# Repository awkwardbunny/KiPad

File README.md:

# KiPad

Custom keypad made using KiCad.

Custom PCB + 3D printed keycaps and case.

# PCB

The PCB was designed in KiCad and manufactured by JLCPCB.

Most of the components have a custom field `DIGIKEY`, which corresponds to the Digikey part number.
Components can be ordered from Digikey easily by doing a BOM export and using Digikey's upload list feature.

The hotswap connectors, key switches, and stablizers do not have Digikey part numbers. Choose ones you like.

# Keycaps

The keycaps were generated using [this library](https://github.com/rsheldiii/KeyV2).

# Case

The PCB was exported from KiCad and a case was modeled around it using OnShape. The models can be found under [case/](/case) or on [OnShape](https://cad.onshape.com/documents/05e5af1ac1cd92aec3ff415b/w/62ce95e3d910c49c77b0c6ec/e/b1757f7efc67fc1a5c9fca3c?renderMode=0&uiState=66b20bf3e3c77e6059daf154).

The bottom of the case is designed to fit 1.2mm thick boards, so keep that in mind when putting in the PCB order.

# Firmware

To build the firmware, follow the [QMK setup](https://docs.qmk.fm/newbs_getting_started), and then copy/link the `qmk` directory into the keyboards directory:

```bash
# Clone project
git clone https://github.com/awkwardbunny/KiPad
cd KiPad
# By default, QMK installs to ~/qmk_firmware on linux
ln -s $(pwd)/qmk ~/qmk_firmware/keyboards/meirl
# Flash. Use the directory name above
qmk flash -kb meirl/kipad_v3_1 -km via
```

## Reset and DFU

The Atmega32u2 goes into DFU bootloader without any code on it. If you wish to reflash, connect the keypad while holding down the top-left key (A).

If a bad firmware was uploaded and you cannot get it into DFU mode with that method, you need to trigger a reset while the `HWB` pin is pulled low.
There is a pad exposed on the back for reset, and the `HWB` pin is connected to column 3. I solder one wire to each of these and do the following:

1. Connect the device
2. Take the wire connected to column 3 and make contact with ground (the USb shield works)
3. Touch the wire connected to the reset pin briefly to ground
4. Release the column 3 wire

And the device should show up in DFU mode

## Via

To use with [Via](https://usevia.app/), you need to enable `Settings -> Show design tab -> Enable`. A new tab should appear.
Open the new design tab and upload the keyboard definition [qmk/kipad_v3_1/via.json](/qmk/kipad_v3_1/via.json). Now you should be able to reconfigure it as you like.

### Udev

For linux, Via may not be able to access the keypad HID devices due to permissions. Try adding the following to `/etc/udev/rules.d/90-kipad.rules`:
```
# MEIRL KiPad v2.0
SUBSYSTEM=="usb", ATTRS{idVendor}=="4248", ATTRS{idProduct}=="4b50", MODE="0666"
KERNEL=="hidraw*", ATTRS{busnum}=="1", ATTRS{idVendor}=="4248", ATTRS{idProduct}=="4b50", MODE="0666"

# MEIRL KiPad v3.0
SUBSYSTEM=="usb", ATTRS{idVendor}=="4248", ATTRS{idProduct}=="4b51", MODE="0666"
KERNEL=="hidraw*", ATTRS{busnum}=="1", ATTRS{idVendor}=="4248", ATTRS{idProduct}=="4b51", MODE="0666"

# MEIRL KiPad v3.1
SUBSYSTEM=="usb", ATTRS{idVendor}=="4248", ATTRS{idProduct}=="4b52", MODE="0666"
KERNEL=="hidraw*", ATTRS{busnum}=="1", ATTRS{idVendor}=="4248", ATTRS{idProduct}=="4b52", MODE="0666"
```

And then `sudo udevadm control --reload`.

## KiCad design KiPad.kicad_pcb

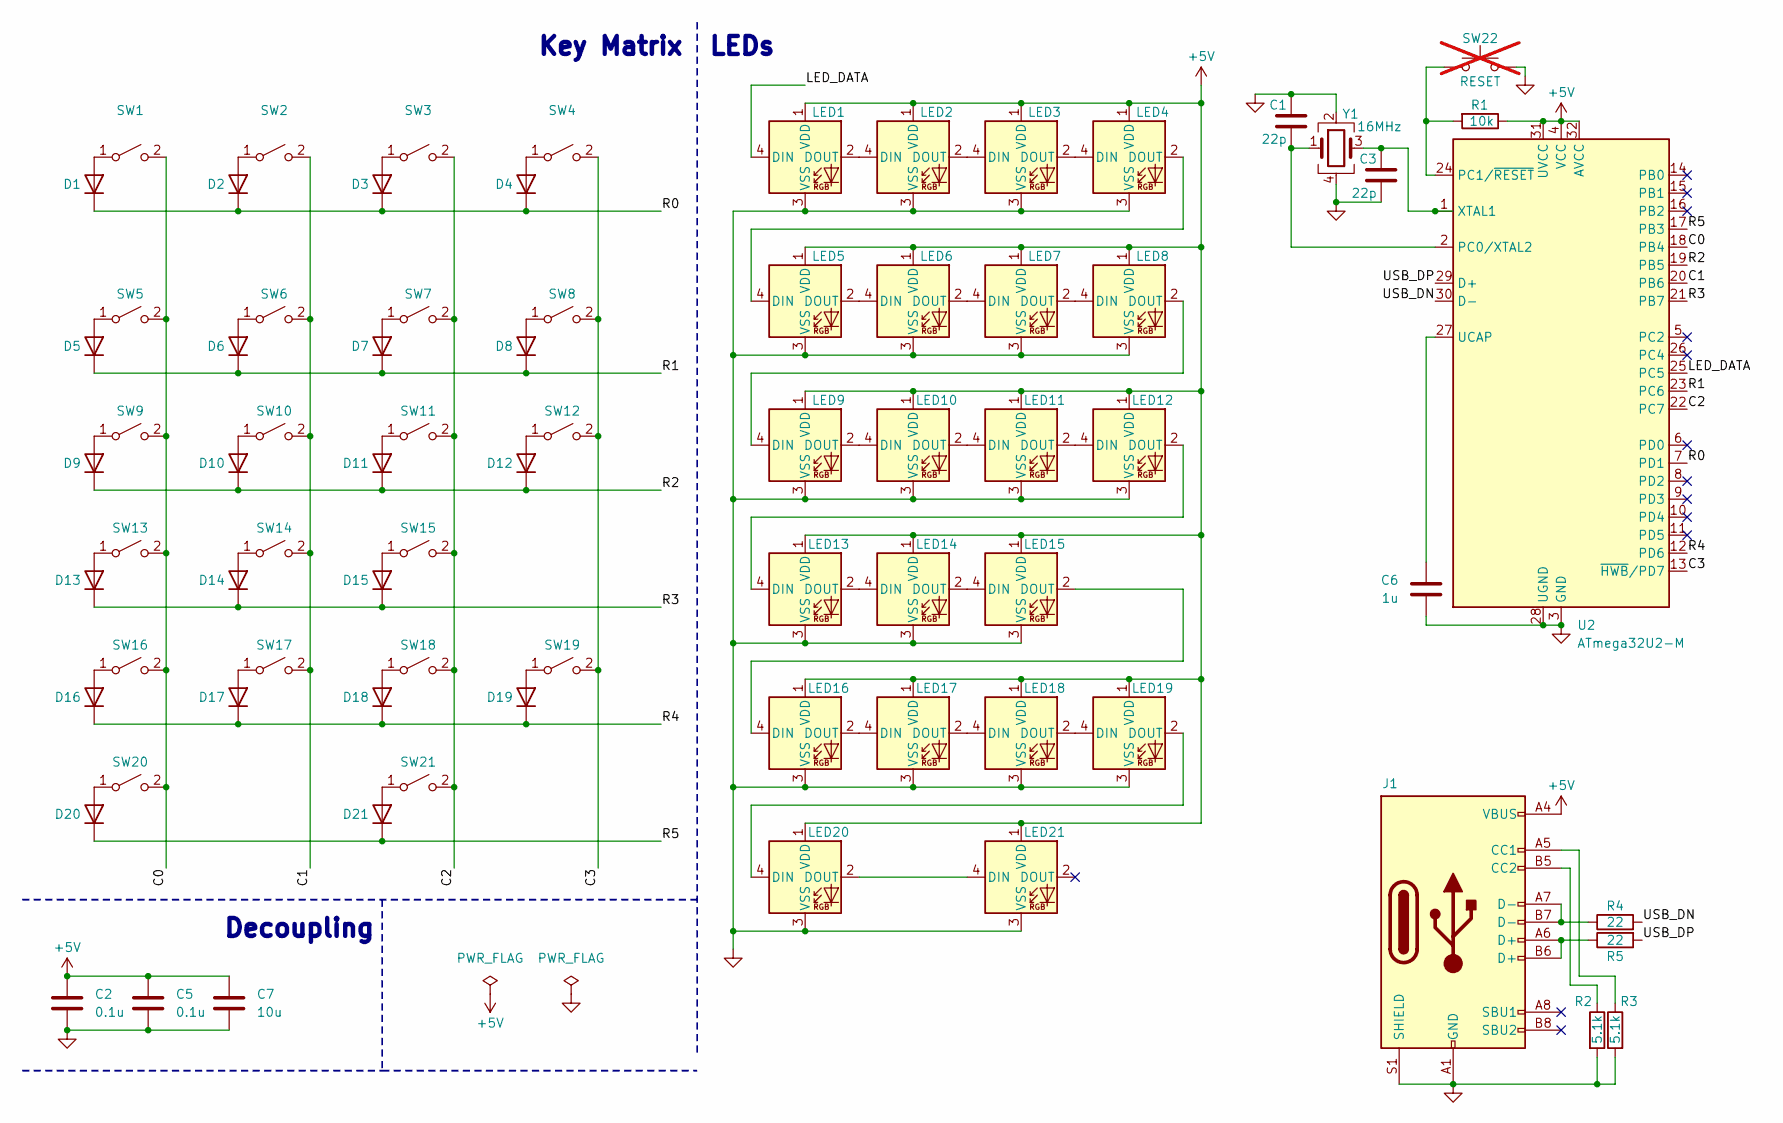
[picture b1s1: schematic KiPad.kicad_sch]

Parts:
C1, C3: 22p; C_0402_1005Metric; DIGIKEY 490-9648-1-ND
C2, C5: 0.1u; C_0805_2012Metric; DIGIKEY 478-KGM21NR71H104KTTR-ND
C6: 1u; C_0603_1608Metric; DIGIKEY 311-1446-1-ND
C7: 10u; C_0805_2012Metric; DIGIKEY 587-1300-1-ND
D1, D2, D3, D4, D5, D6, D7, D8, D9, D10, D11, D12, D13, D14, D15, D16, D17, D18, D19, D20, D21: D_MiniMELF; DIGIKEY FDLL4148TR-ND
J1: USB_C_Receptacle_USB2.0_14P; USB_C_Receptacle_GCT_USB4105-xx-A_16P_TopMnt_Horizontal; DIGIKEY 2073-USB4105-GF-ACT-ND
LED1, LED2, LED3, LED4, LED5, LED6, LED7, LED8, LED9, LED10, LED11, LED12, LED13, LED14, LED15, LED16, LED17, LED18, LED19, LED20, LED21: SK6812MINI; LED_SK6812MINI-E_PLCC4_3.2x2.8mm_P1.75mm; DIGIKEY 1528-4960-ND
R1: 10k; R_0402_1005Metric; DIGIKEY 311-10KJRCT-ND
R2, R3: 5.1k; R_0402_1005Metric; DIGIKEY P5.1KJCT-ND
R4, R5: 22; R_0402_1005Metric; DIGIKEY 311-22.0LRCT-ND
SW1: SW_A; MX-Hotswap-1U
SW2: SW_B; MX-Hotswap-1U
SW3: SW_C; MX-Hotswap-1U
SW4: SW_D; MX-Hotswap-1U
SW5: SW_NL; MX-Hotswap-1U
SW6: SW_DIV; MX-Hotswap-1U
SW7: SW_MUL; MX-Hotswap-1U
SW8: SW_SUB; MX-Hotswap-1U
SW9: SW_7; MX-Hotswap-1U
SW10: SW_8; MX-Hotswap-1U
SW11: SW_9; MX-Hotswap-1U
SW12: SW_ADD; MX-Hotswap-2U-Vertical
SW13: SW_4; MX-Hotswap-1U
SW14: SW_5; MX-Hotswap-1U
SW15: SW_6; MX-Hotswap-1U
SW16: SW_1; MX-Hotswap-1U
SW17: SW_2; MX-Hotswap-1U
SW18: SW_3; MX-Hotswap-1U
SW19: SW_ENTER; MX-Hotswap-2U-Vertical
SW20: SW_0; MX-Hotswap-2U-ReversedStabilizers
SW21: SW_DOT; MX-Hotswap-1U
SW22: RESET; R_0402_1005Metric_Pad0.72x0.64mm_HandSolder; not fitted
U2: ATmega32U2-M; QFN-32-1EP_5x5mm_P0.5mm_EP3.1x3.1mm; DIGIKEY ATMEGA32U2-MURCT-ND
Y1: 16MHz; Crystal_SMD_3225-4Pin_3.2x2.5mm; DIGIKEY 535-14031-1-ND

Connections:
+5V: C2.1, C5.1, C7.1, J1.A4 (VBUS), J1.A9 (VBUS), J1.B4 (VBUS), J1.B9 (VBUS), LED1.1 (VDD), LED2.1 (VDD), LED3.1 (VDD), LED4.1 (VDD), LED5.1 (VDD), LED6.1 (VDD), LED7.1 (VDD), LED8.1 (VDD), LED9.1 (VDD), LED10.1 (VDD), LED11.1 (VDD), LED12.1 (VDD), LED13.1 (VDD), LED14.1 (VDD), LED15.1 (VDD), LED16.1 (VDD), LED17.1 (VDD), LED18.1 (VDD), LED19.1 (VDD), LED20.1 (VDD), LED21.1 (VDD), R1.1, U2.4 (VCC), U2.31 (UVCC), U2.32 (AVCC)
/C0: SW1.2 (B), SW5.2 (B), SW9.2 (B), SW13.2 (B), SW16.2 (B), SW20.2 (B), U2.18 (PB4)
/C1: SW2.2 (B), SW6.2 (B), SW10.2 (B), SW14.2 (B), SW17.2 (B), U2.20 (PB6)
/C2: SW3.2 (B), SW7.2 (B), SW11.2 (B), SW15.2 (B), SW18.2 (B), SW21.2 (B), U2.22 (PC7)
/C3: SW4.2 (B), SW8.2 (B), SW12.2 (B), SW19.2 (B), U2.13 (~HWB/PD7)
/LED_DATA: LED1.4 (DIN), U2.25 (PC5)
/R0: D1.1 (K), D2.1 (K), D3.1 (K), D4.1 (K), U2.7 (PD1)
/R1: D5.1 (K), D6.1 (K), D7.1 (K), D8.1 (K), U2.23 (PC6)
/R2: D9.1 (K), D10.1 (K), D11.1 (K), D12.1 (K), U2.19 (PB5)
/R3: D13.1 (K), D14.1 (K), D15.1 (K), U2.21 (PB7)
/R4: D16.1 (K), D17.1 (K), D18.1 (K), D19.1 (K), U2.12 (PD6)
/R5: D20.1 (K), D21.1 (K), U2.17 (PB3)
/USB_DN: R4.2, U2.30 (D-)
/USB_DP: R5.2, U2.29 (D+)
GND: C1.1, C2.2, C3.2, C5.2, C6.2, C7.2, J1.A1 (GND), J1.A12 (GND), J1.B1 (GND), J1.B12 (GND), J1.S1 (SHIELD), LED1.3 (VSS), LED2.3 (VSS), LED3.3 (VSS), LED4.3 (VSS), LED5.3 (VSS), LED6.3 (VSS), LED7.3 (VSS), LED8.3 (VSS), LED9.3 (VSS), LED10.3 (VSS), LED11.3 (VSS), LED12.3 (VSS), LED13.3 (VSS), LED14.3 (VSS), LED15.3 (VSS), LED16.3 (VSS), LED17.3 (VSS), LED18.3 (VSS), LED19.3 (VSS), LED20.3 (VSS), LED21.3 (VSS), R2.2, R3.2, SW22.2, U2.3 (GND), U2.28 (UGND), U2.33 (GND), Y1.2, Y1.4
unnamed: D1.2 (A), SW1.1 (A)
unnamed: D2.2 (A), SW2.1 (A)
unnamed: D3.2 (A), SW3.1 (A)
unnamed: D4.2 (A), SW4.1 (A)
unnamed: D5.2 (A), SW5.1 (A)
unnamed: D6.2 (A), SW6.1 (A)
unnamed: D7.2 (A), SW7.1 (A)
unnamed: D8.2 (A), SW8.1 (A)
unnamed: D9.2 (A), SW9.1 (A)
unnamed: D10.2 (A), SW10.1 (A)
unnamed: D11.2 (A), SW11.1 (A)
unnamed: D12.2 (A), SW12.1 (A)
unnamed: D13.2 (A), SW13.1 (A)
unnamed: D14.2 (A), SW14.1 (A)
unnamed: D15.2 (A), SW15.1 (A)
unnamed: D16.2 (A), SW16.1 (A)
unnamed: D17.2 (A), SW17.1 (A)
unnamed: D18.2 (A), SW18.1 (A)
unnamed: D19.2 (A), SW19.1 (A)
unnamed: D20.2 (A), SW20.1 (A)
unnamed: D21.2 (A), SW21.1 (A)
unnamed: J1.A5 (CC1), R3.1
unnamed: J1.B5 (CC2), R2.1
unnamed: J1.A6 (D+), J1.B6 (D+), R5.1
unnamed: J1.A7 (D-), J1.B7 (D-), R4.1
unnamed: LED1.2 (DOUT), LED2.4 (DIN)
unnamed: LED2.2 (DOUT), LED3.4 (DIN)
unnamed: LED3.2 (DOUT), LED4.4 (DIN)
unnamed: LED4.2 (DOUT), LED5.4 (DIN)
unnamed: LED5.2 (DOUT), LED6.4 (DIN)
unnamed: LED6.2 (DOUT), LED7.4 (DIN)
unnamed: LED7.2 (DOUT), LED8.4 (DIN)
unnamed: LED8.2 (DOUT), LED9.4 (DIN)
unnamed: LED9.2 (DOUT), LED10.4 (DIN)
unnamed: LED10.2 (DOUT), LED11.4 (DIN)
unnamed: LED11.2 (DOUT), LED12.4 (DIN)
unnamed: LED12.2 (DOUT), LED13.4 (DIN)
unnamed: LED13.2 (DOUT), LED14.4 (DIN)
unnamed: LED14.2 (DOUT), LED15.4 (DIN)
unnamed: LED15.2 (DOUT), LED16.4 (DIN)
unnamed: LED16.2 (DOUT), LED17.4 (DIN)
unnamed: LED17.2 (DOUT), LED18.4 (DIN)
unnamed: LED18.2 (DOUT), LED19.4 (DIN)
unnamed: LED19.2 (DOUT), LED20.4 (DIN)
unnamed: LED20.2 (DOUT), LED21.4 (DIN)
unnamed: C1.2, U2.2 (PC0/XTAL2), Y1.1
unnamed: R1.2, SW22.1, U2.24 (PC1/~RESET)
unnamed: C6.1, U2.27 (UCAP)
unnamed: C3.1, U2.1 (XTAL1), Y1.3

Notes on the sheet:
Key Matrix
LEDs
Decoupling

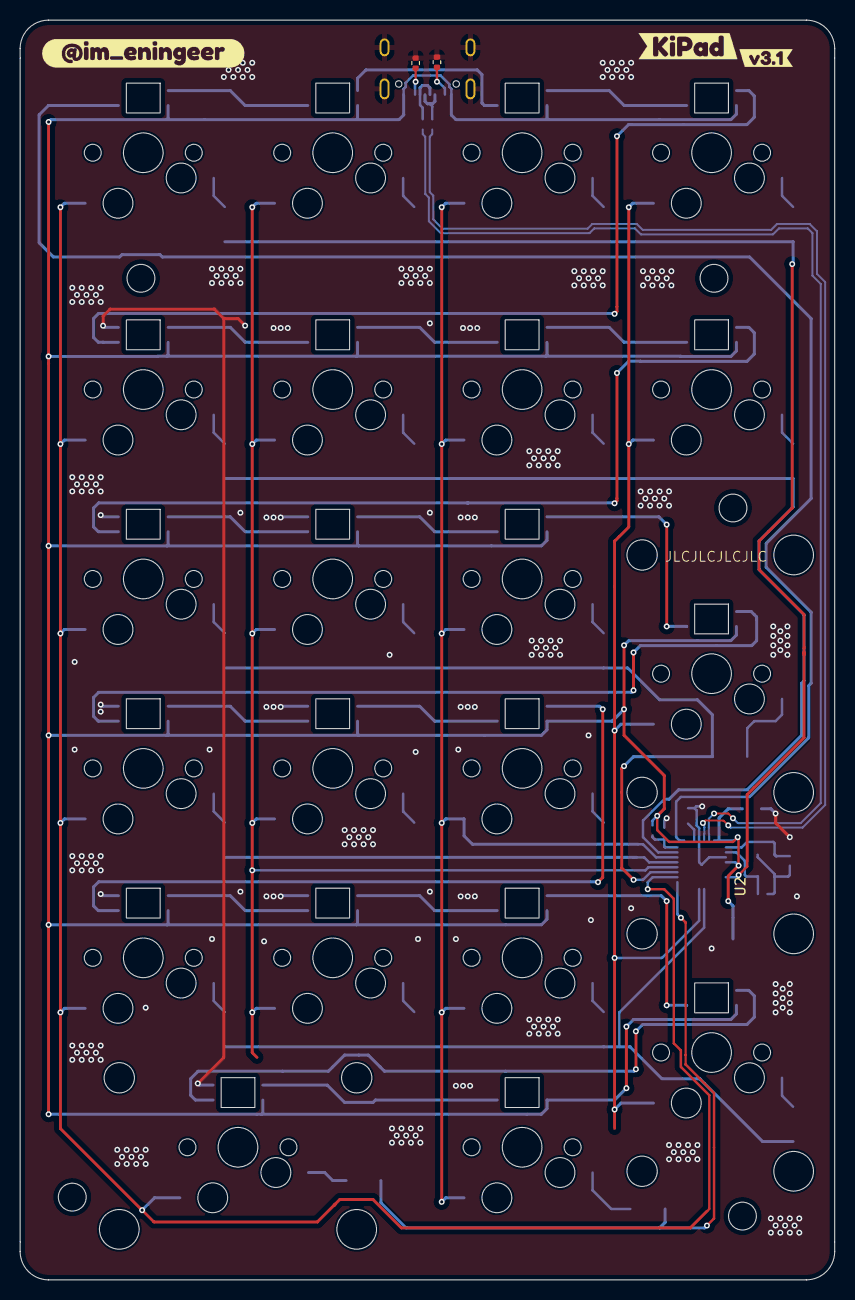
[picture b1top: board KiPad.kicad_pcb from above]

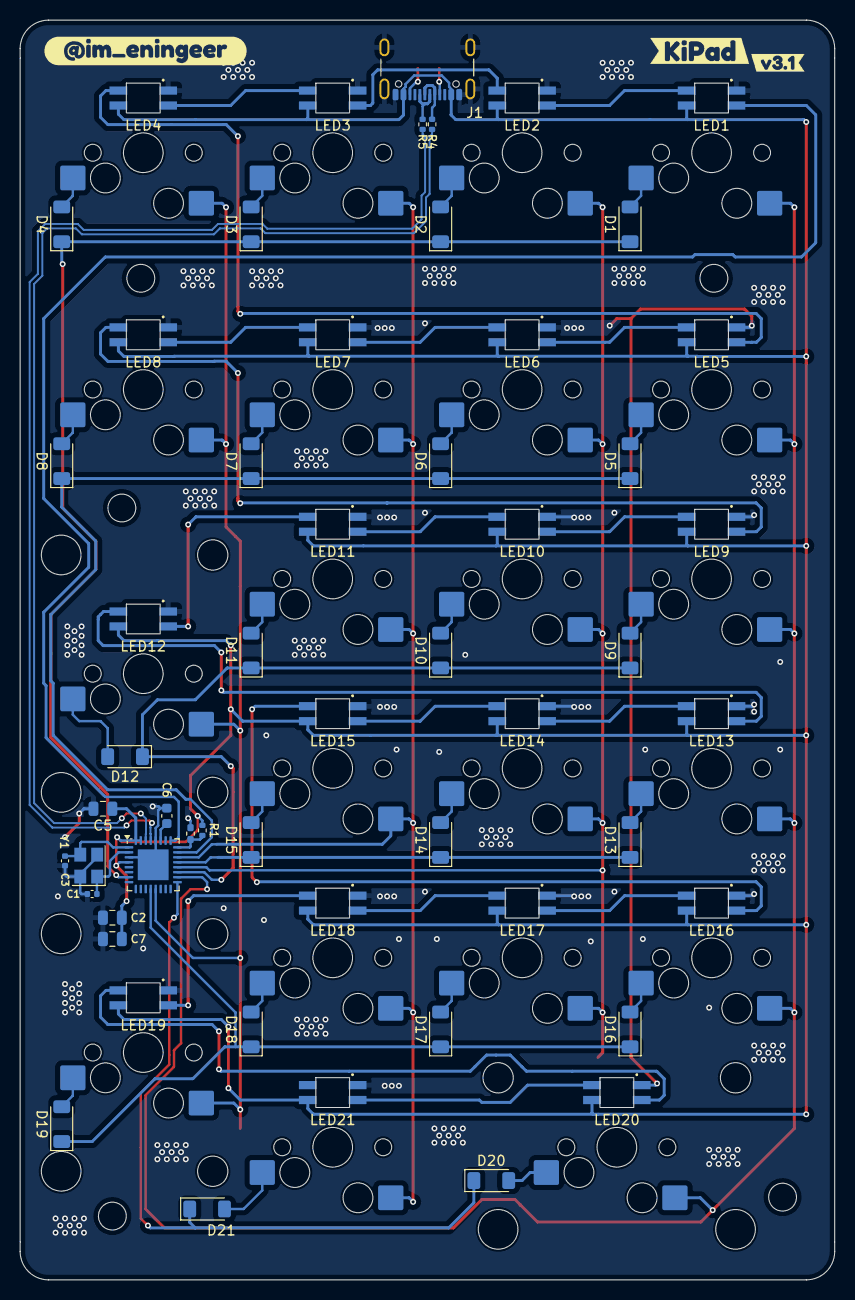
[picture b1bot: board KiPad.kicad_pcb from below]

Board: 2 copper layers, 81.9 x 126.7 mm, 84 parts (58 on the bottom side), 64 nets.

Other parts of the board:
kibuzzard-66A8A61F, kibuzzard-66A8A61F#2: G***; kibuzzard-66A8A61F
kibuzzard-66A8A64C, kibuzzard-66A8A64C#2: G***; kibuzzard-66A8A64C
kibuzzard-66A8A670, kibuzzard-66A8A670#2: G***; kibuzzard-66A8A670

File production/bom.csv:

Designator,Footprint,Quantity,Value,LCSC Part #
"C1, C3",0402,2,22p,
"C2, C5",0805,2,0.1u,
C6,0603,1,1u,
C7,0805,1,10u,
"D1, D10, D11, D12, D13, D14, D15, D16, D17, D18, D19, D2, D20, D21, D3, D4, D5, D6, D7, D8, D9",D_MiniMELF,21,~,
J1,USB_C_Receptacle_GCT_USB4105-xx-A_16P_TopMnt_Horizontal,1,USB_C_Receptacle_USB2.0_14P,
"LED1, LED10, LED11, LED12, LED13, LED14, LED15, LED16, LED17, LED18, LED19, LED2, LED20, LED21, LED3, LED4, LED5, LED6, LED7, LED8, LED9",LED_SK6812MINI-E_PLCC4_3.2x2.8mm_P1.75mm,21,SK6812MINI,
R1,0402,1,10k,
"R2, R3",0402,2,5.1k,
"R4, R5",0402,2,22,
SW1,MX-Hotswap-1U,1,SW_A,
SW10,MX-Hotswap-1U,1,SW_8,
SW11,MX-Hotswap-1U,1,SW_9,
SW12,MX-Hotswap-2U-Vertical,1,SW_ADD,
SW13,MX-Hotswap-1U,1,SW_4,
SW14,MX-Hotswap-1U,1,SW_5,
SW15,MX-Hotswap-1U,1,SW_6,
SW16,MX-Hotswap-1U,1,SW_1,
SW17,MX-Hotswap-1U,1,SW_2,
SW18,MX-Hotswap-1U,1,SW_3,
SW19,MX-Hotswap-2U-Vertical,1,SW_ENTER,
SW2,MX-Hotswap-1U,1,SW_B,
SW20,MX-Hotswap-2U-ReversedStabilizers,1,SW_0,
SW21,MX-Hotswap-1U,1,SW_DOT,
SW22,0402,1,RESET,
SW3,MX-Hotswap-1U,1,SW_C,
SW4,MX-Hotswap-1U,1,SW_D,
SW5,MX-Hotswap-1U,1,SW_NL,
SW6,MX-Hotswap-1U,1,SW_DIV,
SW7,MX-Hotswap-1U,1,SW_MUL,
SW8,MX-Hotswap-1U,1,SW_SUB,
SW9,MX-Hotswap-1U,1,SW_7,
U2,QFN-32-1EP_5x5mm_P0.5mm_EP3.1x3.1mm,1,ATmega32U2-M,
Y1,Crystal_SMD_3225-4Pin_3.2x2.5mm,1,16MHz,

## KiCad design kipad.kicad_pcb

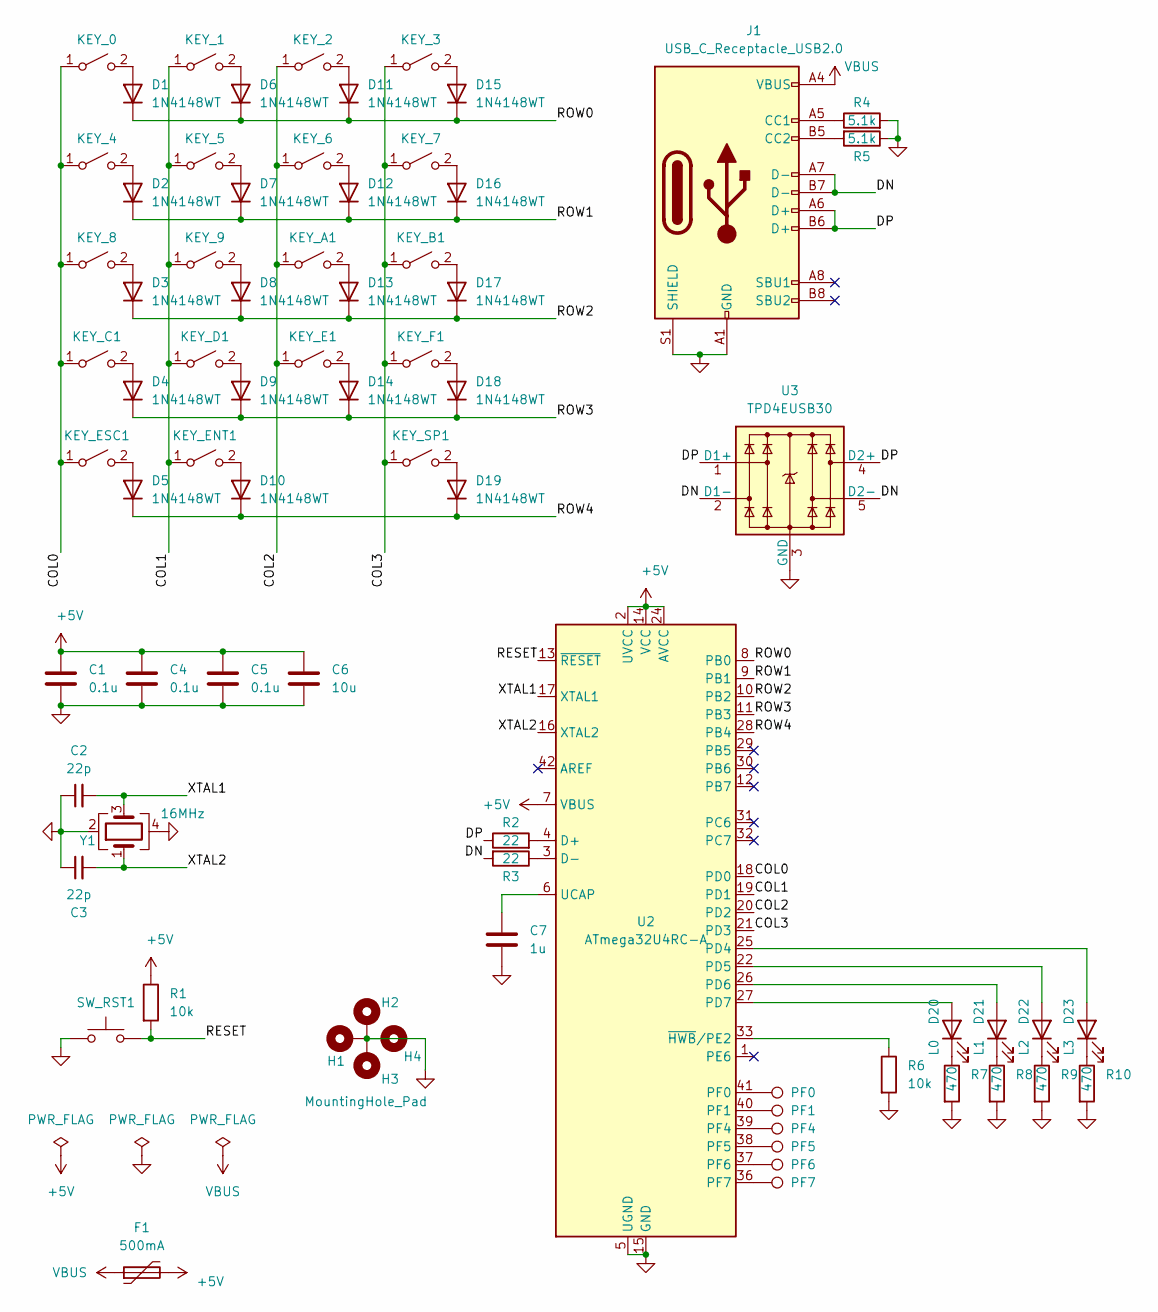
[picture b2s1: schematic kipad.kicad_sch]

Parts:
C1, C4, C5: 0.1u; C_0805_2012Metric
C2, C3: 22p; C_0805_2012Metric
C6: 10u; C_0805_2012Metric
C7: 1u; C_0805_2012Metric
D1, D2, D3, D4, D5, D6, D7, D8, D9, D10, D11, D12, D13, D14, D15, D16, D17, D18, D19: 1N4148WT; D_SOD-523
D20: L0; LED_1206_3216Metric
D21: L1; LED_1206_3216Metric
D22: L2; LED_1206_3216Metric
D23: L3; LED_1206_3216Metric
F1: 500mA; Fuse_1206_3216Metric
H1, H2, H3, H4: MountingHole_Pad; MountingHole_2.2mm_M2_Pad
J1: USB_C_Receptacle_USB2.0; USB_C_Receptacle_Amphenol_12401610E4-2A
KEY_0, KEY_1, KEY_2, KEY_3, KEY_4, KEY_5, KEY_6, KEY_7, KEY_8, KEY_9: SW_SPST; SW_Cherry_MX_1.00u_PCB
KEY_A1: SW_SPST; SW_Cherry_MX_1.00u_PCB
KEY_B1: SW_SPST; SW_Cherry_MX_1.00u_PCB
KEY_C1: SW_SPST; SW_Cherry_MX_1.00u_PCB
KEY_D1: SW_SPST; SW_Cherry_MX_1.00u_PCB
KEY_E1: SW_SPST; SW_Cherry_MX_1.00u_PCB
KEY_ENT1: SW_SPST; SW_Cherry_MX_2.00u_PCB
KEY_ESC1: SW_SPST; SW_Cherry_MX_1.00u_PCB
KEY_F1: SW_SPST; SW_Cherry_MX_1.00u_PCB
KEY_SP1: SW_SPST; SW_Cherry_MX_1.00u_PCB
PF0, PF1, PF4, PF5, PF6, PF7: TestPoint; TestPoint_Pad_1.0x1.0mm
R1, R6: 10k; R_0805_2012Metric
R2, R3: 22; R_0805_2012Metric
R4, R5: 5.1k; R_0805_2012Metric
R7, R8, R9, R10: 470; R_0805_2012Metric
SW_RST1: SW_Push; SW_SPST_TL3342
U2: ATmega32U4RC-A; TQFP-44_10x10mm_P0.8mm
U3: TPD4EUSB30; USON-10_2.5x1.0mm_P0.5mm
Y1: 16MHz; Crystal_SMD_3225-4Pin_3.2x2.5mm

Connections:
+5V: C1.1, C4.1, C5.1, C6.1, F1.2, R1.1, U2.2 (UVCC), U2.7 (VBUS), U2.14 (VCC), U2.24 (AVCC), U2.34 (VCC), U2.44 (AVCC)
/COL0: KEY_0.1 (A), KEY_4.1 (A), KEY_8.1 (A), KEY_C1.1 (A), KEY_ESC1.1 (A), U2.18 (PD0)
/COL1: KEY_1.1 (A), KEY_5.1 (A), KEY_9.1 (A), KEY_D1.1 (A), KEY_ENT1.1 (A), U2.19 (PD1)
/COL2: KEY_2.1 (A), KEY_6.1 (A), KEY_A1.1 (A), KEY_E1.1 (A), U2.20 (PD2)
/COL3: KEY_3.1 (A), KEY_7.1 (A), KEY_B1.1 (A), KEY_F1.1 (A), KEY_SP1.1 (A), U2.21 (PD3)
/DN: J1.A7 (D-), J1.B7 (D-), R3.2, U3.2 (D1-), U3.5 (D2-)
/DP: J1.A6 (D+), J1.B6 (D+), R2.1, U3.1 (D1+), U3.4 (D2+)
/RESET: R1.2, SW_RST1.2, U2.13 (~RESET)
/ROW0: D1.1 (K), D6.1 (K), D11.1 (K), D15.1 (K), U2.8 (PB0)
/ROW1: D2.1 (K), D7.1 (K), D12.1 (K), D16.1 (K), U2.9 (PB1)
/ROW2: D3.1 (K), D8.1 (K), D13.1 (K), D17.1 (K), U2.10 (PB2)
/ROW3: D4.1 (K), D9.1 (K), D14.1 (K), D18.1 (K), U2.11 (PB3)
/ROW4: D5.1 (K), D10.1 (K), D19.1 (K), U2.28 (PB4)
/XTAL1: C2.2, U2.17 (XTAL1), Y1.3
/XTAL2: C3.2, U2.16 (XTAL2), Y1.1
GND: C1.2, C2.1, C3.1, C4.2, C5.2, C6.2, C7.2, H1.1, H2.1, H3.1, H4.1, J1.A1 (GND), J1.A12 (GND), J1.B1 (GND), J1.B12 (GND), J1.S1 (SHIELD), R4.2, R5.1, R6.2, R7.2, R8.2, R9.2, R10.2, SW_RST1.1, U2.5 (UGND), U2.15 (GND), U2.23 (GND), U2.35 (GND), U2.43 (GND), U3.3 (GND), U3.8 (GND), Y1.2, Y1.4
unnamed: C7.1, U2.6 (UCAP)
unnamed: D1.2 (A), KEY_0.2 (B)
unnamed: D2.2 (A), KEY_4.2 (B)
unnamed: D3.2 (A), KEY_8.2 (B)
unnamed: D4.2 (A), KEY_C1.2 (B)
unnamed: D5.2 (A), KEY_ESC1.2 (B)
unnamed: D6.2 (A), KEY_1.2 (B)
unnamed: D7.2 (A), KEY_5.2 (B)
unnamed: D8.2 (A), KEY_9.2 (B)
unnamed: D9.2 (A), KEY_D1.2 (B)
unnamed: D10.2 (A), KEY_ENT1.2 (B)
unnamed: D11.2 (A), KEY_2.2 (B)
unnamed: D12.2 (A), KEY_6.2 (B)
unnamed: D13.2 (A), KEY_A1.2 (B)
unnamed: D14.2 (A), KEY_E1.2 (B)
unnamed: D15.2 (A), KEY_3.2 (B)
unnamed: D16.2 (A), KEY_7.2 (B)
unnamed: D17.2 (A), KEY_B1.2 (B)
unnamed: D18.2 (A), KEY_F1.2 (B)
unnamed: D19.2 (A), KEY_SP1.2 (B)
unnamed: D20.1 (K), R7.1
unnamed: D20.2 (A), U2.27 (PD7)
unnamed: D21.1 (K), R8.1
unnamed: D21.2 (A), U2.26 (PD6)
unnamed: D22.1 (K), R9.1
unnamed: D22.2 (A), U2.22 (PD5)
unnamed: D23.1 (K), R10.1
unnamed: D23.2 (A), U2.25 (PD4)
unnamed: J1.A5 (CC1), R4.1
unnamed: J1.B5 (CC2), R5.2
unnamed: PF0.1, U2.41 (PF0)
unnamed: PF1.1, U2.40 (PF1)
unnamed: PF4.1, U2.39 (PF4)
unnamed: PF5.1, U2.38 (PF5)
unnamed: PF6.1, U2.37 (PF6)
unnamed: PF7.1, U2.36 (PF7)
unnamed: R2.2, U2.4 (D+)
unnamed: R3.1, U2.3 (D-)
unnamed: R6.1, U2.33 (~HWB~/PE2)
VBUS: F1.1, J1.A4 (VBUS), J1.A9 (VBUS), J1.B4 (VBUS), J1.B9 (VBUS)

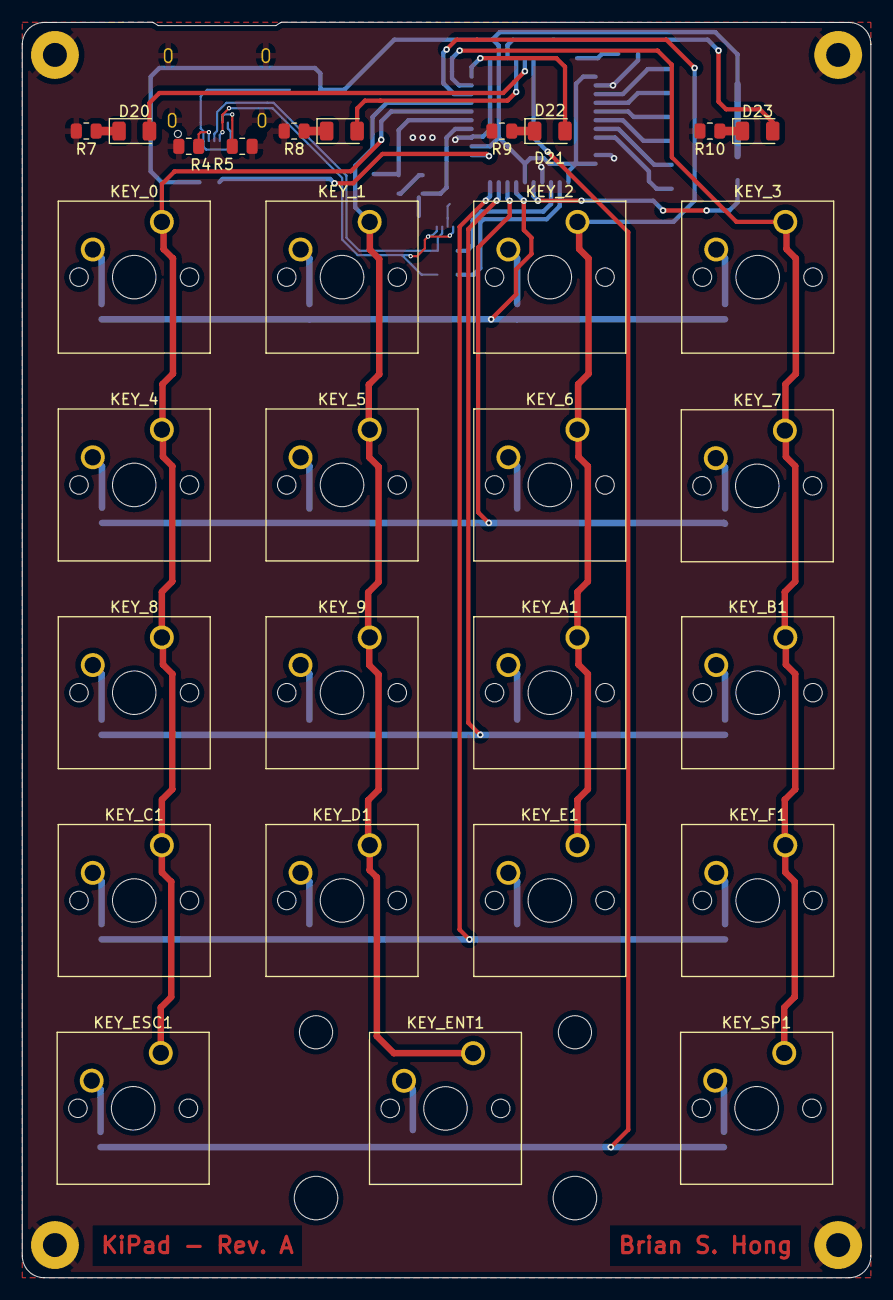
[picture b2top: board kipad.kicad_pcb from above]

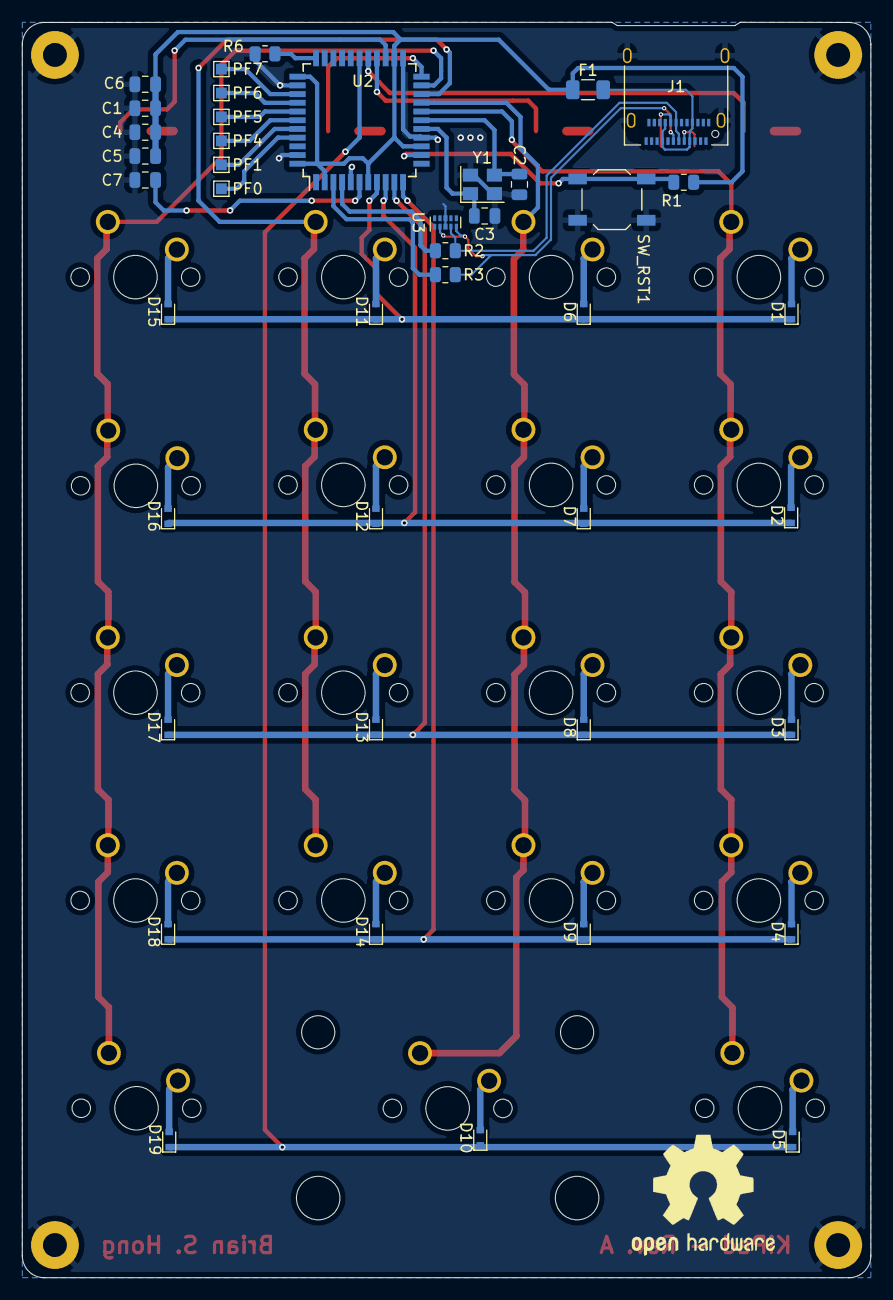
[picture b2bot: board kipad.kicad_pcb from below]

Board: 2 copper layers, 78.0 x 115.4 mm, 75 parts (42 on the bottom side), 56 nets.

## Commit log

2021-04-26 Initial design
2021-05-20 Added NOTES.md
2024-06-22 AHHHHH
2024-07-30 v3.1
    Flip around stabs so the shaft is on the outside.
    Fix LED footprint and reroute.
2024-08-06 Add QMK code
2024-08-06 Add images
2024-08-06 Added case models
